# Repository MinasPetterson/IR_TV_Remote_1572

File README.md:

Controle remoto IR para qualquer TV, usando o PIC 12f1572 sem cristal, operando a 32Mhz.
IR remote control for any TV, using the PIC 12f1572 without crystal, operating at 32Mhz.

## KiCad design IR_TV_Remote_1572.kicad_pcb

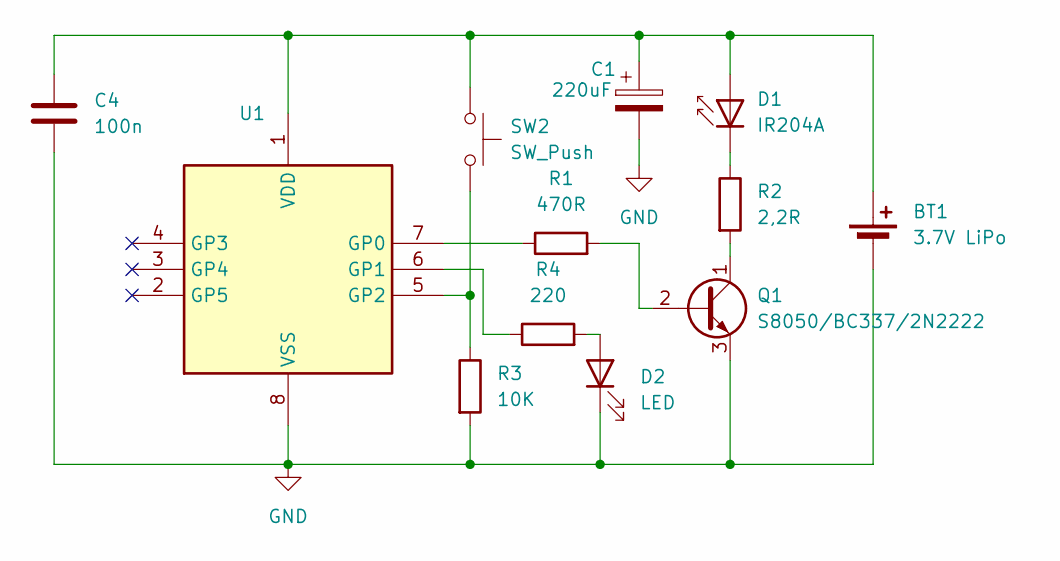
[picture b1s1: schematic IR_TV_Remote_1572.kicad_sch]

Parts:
BT1: 3.7V LiPo; Battery_Panasonic_CR2032-HFN_Horizontal_CircularHoles
C1: 220uF; CP_Radial_D5.0mm_P2.00mm
C4: 100n; C_Disc_D4.7mm_W2.5mm_P5.00mm
D1: IR204A; LED_D3.0mm_IRBlack
D2: LED; LED_D3.0mm_Clear
Q1: S8050/BC337/2N2222; TO-92_Inline_Wide
R1: 470R; R_Axial_DIN0207_L6.3mm_D2.5mm_P7.62mm_Horizontal
R2: 2,2R; R_Axial_DIN0207_L6.3mm_D2.5mm_P7.62mm_Horizontal
R3: 10K; R_Axial_DIN0207_L6.3mm_D2.5mm_P7.62mm_Horizontal
R4: 220; R_Axial_DIN0207_L6.3mm_D2.5mm_P7.62mm_Horizontal
SW2: SW_Push; SW_TH_Tactile_Omron_B3F-100x
U1: PIC12F675; JEITA_SOIC-8_3.9x4.9mm_P1.27mm

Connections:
GND: BT1.2 (-), C1.2, C4.1, D2.1 (K), Q1.3 (E), R3.2, U1.8 (VSS)
unnamed: BT1.1 (+), C1.1, C4.2, D1.2 (A), SW2.1, U1.1 (VDD)
unnamed: D1.1 (K), R2.1
unnamed: D2.2 (A), R4.2
unnamed: Q1.2 (B), R1.2
unnamed: Q1.1 (C), R2.2
unnamed: R1.1, U1.7 (GP0)
unnamed: R4.1, U1.6 (GP1)
unnamed: R3.1, SW2.2, U1.5 (GP2)

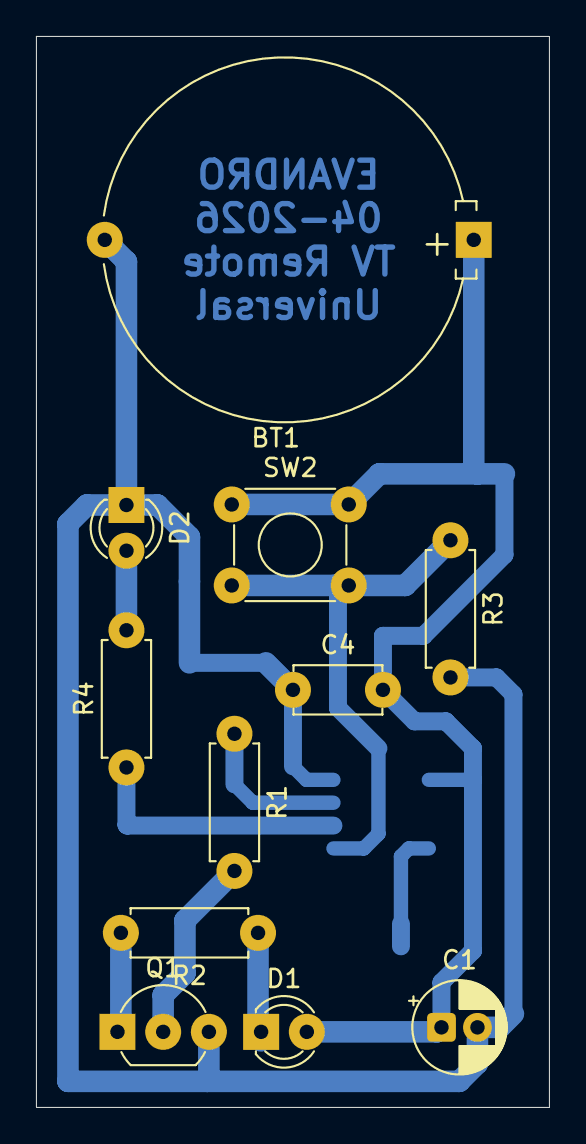
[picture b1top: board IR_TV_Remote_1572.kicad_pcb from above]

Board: 2 copper layers, 28.5 x 59.5 mm, 12 parts (1 on the bottom side), 9 nets.

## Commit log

2026-04-24 Add project description in Portuguese and English
    Controle remoto IR para qualquer TV, usando o PIC 12f1572 sem cristal, operando a 32Mhz.
    IR remote control for any TV, using the PIC 12f1572 without crystal, operating at 32Mhz.
